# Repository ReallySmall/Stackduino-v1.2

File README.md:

Stackduino v1.2
==========
Please visit the project site for details: https://www.stackduino.net/boards/v1_2

Copyright 2017 Richard Iles

Permission is hereby granted, free of charge, to any person obtaining a copy of this software and associated documentation files (the "Software"), to deal in the Software without restriction, including without limitation the rights to use, copy, modify, merge, publish, distribute, sublicense, and/or sell copies of the Software, and to permit persons to whom the Software is furnished to do so, subject to the following conditions:

The above copyright notice and this permission notice shall be included in all copies or substantial portions of the Software.

THE SOFTWARE IS PROVIDED "AS IS", WITHOUT WARRANTY OF ANY KIND, EXPRESS OR IMPLIED, INCLUDING BUT NOT LIMITED TO THE WARRANTIES OF MERCHANTABILITY, FITNESS FOR A PARTICULAR PURPOSE AND NONINFRINGEMENT. IN NO EVENT SHALL THE AUTHORS OR COPYRIGHT HOLDERS BE LIABLE FOR ANY CLAIM, DAMAGES OR OTHER LIABILITY, WHETHER IN AN ACTION OF CONTRACT, TORT OR OTHERWISE, ARISING FROM, OUT OF OR IN CONNECTION WITH THE SOFTWARE OR THE USE OR OTHER DEALINGS IN THE SOFTWARE.

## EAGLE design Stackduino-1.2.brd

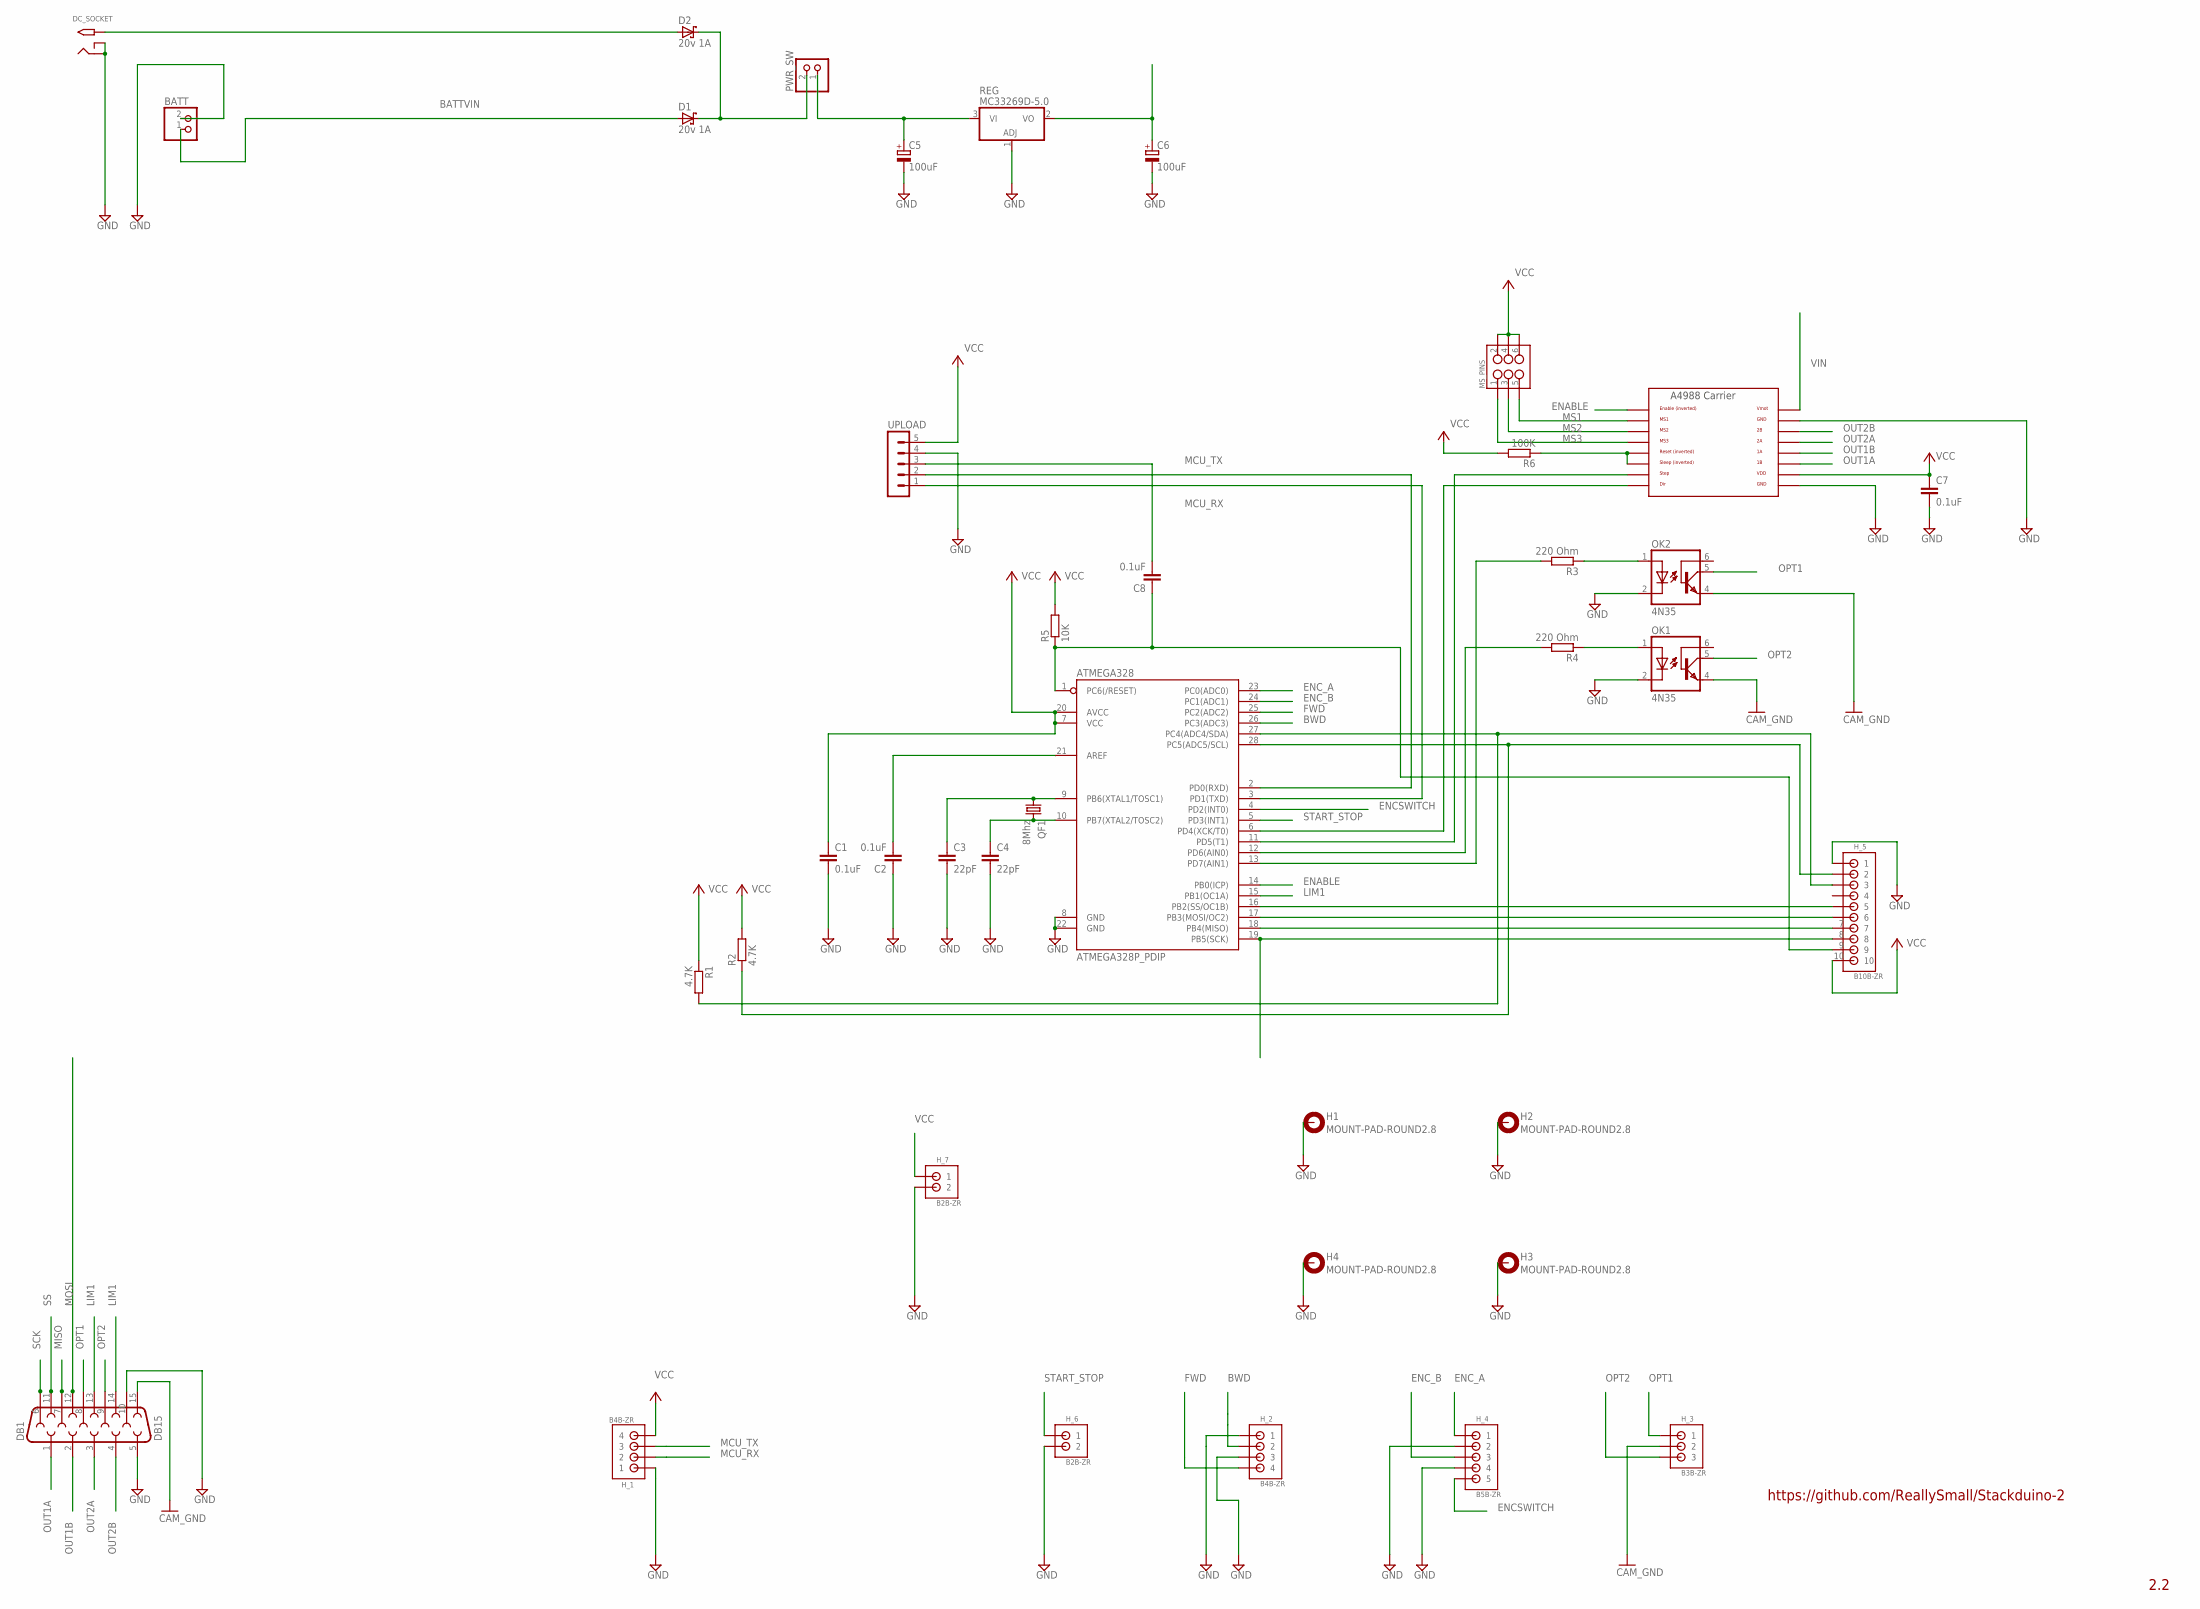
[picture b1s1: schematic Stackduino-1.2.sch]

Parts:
A4988_CARRIER: A4988BREAKOUT
ATMEGA328: ATMEGA328P_PDIP; DIL28-3
BATT: JST_2PIN-THM; JST-PH-2-THM
C1, C2, C7, C8: 0.1uF; C025-030X050
C3, C4: 22pF; C025-030X050
C5, C6: 100uF; E2,5-7
D1, D2: 20v 1A; DO41-10
DB1: DB15
DC_SOCKET: 2.1MMJACKTHM; PJ-102A
H1, H2, H3, H4: MOUNT-PAD-ROUND2.8; 2,8-PAD
H_1, H_2: B4B-ZR
H_3: B3B-ZR
H_4: B5B-ZR
H_5: B10B-ZR
H_6, H_7: B2B-ZR
MS_PINS: M03X22X3_SILK_MALE_PTH; 2X3
OK1, OK2: 4N35; DIL06
PWR_SW: JST_2PIN-THM; JST-PH-2-THM
QF1: 8Mhz; HC49U-V
R1, R2: 4.7K; 0207/7
R3, R4: 220 Ohm; 0207/7
R5: 10K; 0207/7
R6: 100K; 0207/7
REG: MC33269D-5.0; DPACK
UPLOAD: MA05-1

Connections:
A4988_RESET: A4988_CARRIER.RST, A4988_CARRIER.SLP (SLEEP), R6.1
ACVIN: D2.A, DC_SOCKET.TIP
BATTVIN: BATT.1 (2), D1.A
BWD: ATMEGA328.26 (PC3(ADC3)), H_2.2
CAM_GND: DB1.15, H_3.2, OK1.4 (EMI), OK2.4 (EMI)
DIR: A4988_CARRIER.DIR, ATMEGA328.6 (PD4(XCK/T0))
ENABLE: A4988_CARRIER.EN, ATMEGA328.14 (PB0(ICP))
ENCSWITCH: ATMEGA328.4 (PD2(INT0)), H_4.5
ENC_A: ATMEGA328.23 (PC0(ADC0)), H_4.1
ENC_B: ATMEGA328.24 (PC1(ADC1)), H_4.3
FWD: ATMEGA328.25 (PC2(ADC2)), H_2.4
GND: A4988_CARRIER.GND, A4988_CARRIER.GND@0 (GND), ATMEGA328.8 (GND), ATMEGA328.22 (GND), BATT.2 (1), C1.2, C2.1, C3.2, C4.2, C5.-, C6.-, C7.2, DB1.5, DB1.10, DC_SOCKET.RING, DC_SOCKET.RING_SW, H1.B2,8, H2.B2,8, H3.B2,8, H4.B2,8, H_1.1, H_2.1, H_2.3, H_4.2, H_4.4, H_5.1, H_6.2, H_7.2, OK1.2 (C), OK2.2 (C), REG.1 (ADJ), UPLOAD.4
I2C_SCL: ATMEGA328.28 (PC5(ADC5/SCL)), H_5.2, R2.1
I2C_SDA: ATMEGA328.27 (PC4(ADC4/SDA)), H_5.3, R1.2
LIM1: ATMEGA328.15 (PB1(OC1A)), DB1.13, DB1.14
MCU_RX: ATMEGA328.2 (PD0(RXD)), H_1.2, UPLOAD.2
MCU_TX: ATMEGA328.3 (PD1(TXD)), H_1.3, UPLOAD.1
MISO: ATMEGA328.18 (PB4(MISO)), DB1.7, H_5.7
MOSI: ATMEGA328.17 (PB3(MOSI/OC2)), DB1.12, H_5.6
MS1: A4988_CARRIER.MS1, MS_PINS.5
MS2: A4988_CARRIER.MS2, MS_PINS.3
MS3: A4988_CARRIER.MS3, MS_PINS.1
unnamed: D1.C, D2.C, PWR_SW.2 (1)
unnamed: ATMEGA328.1 (PC6(/RESET)), C8.1, H_5.9, R5.1
unnamed: C8.2, UPLOAD.3
unnamed: ATMEGA328.21 (AREF), C2.2
OPT1: DB1.8, H_3.1, OK2.5 (COL)
OPT1_IN: OK2.1 (A), R3.1
OPT1_MCU: ATMEGA328.13 (PD7(AIN1)), R3.2
OPT2: DB1.9, H_3.3, OK1.5 (COL)
OPT2_IN: OK1.1 (A), R4.1
OPT2_MCU: ATMEGA328.12 (PD6(AIN0)), R4.2
OUT1A: A4988_CARRIER.1B, DB1.1
OUT1B: A4988_CARRIER.1A, DB1.2
OUT2A: A4988_CARRIER.2A, DB1.3
OUT2B: A4988_CARRIER.2B, DB1.4
SCK: ATMEGA328.19 (PB5(SCK)), DB1.6, H_5.8
SS: ATMEGA328.16 (PB2(SS/OC1B)), DB1.11, H_5.5
START_STOP: ATMEGA328.5 (PD3(INT1)), H_6.1
STEP: A4988_CARRIER.STEP, ATMEGA328.11 (PD5(T1))
VCC: A4988_CARRIER.VDD, ATMEGA328.7 (VCC), ATMEGA328.20 (AVCC), C1.1, C6.+, C7.1, H_1.4, H_5.10, H_7.1, MS_PINS.2, MS_PINS.4, MS_PINS.6, R1.1, R2.2, R5.2, R6.2, REG.2 (VO), UPLOAD.5
VIN: A4988_CARRIER.VMOT, C5.+, PWR_SW.1 (2), REG.3 (VI)
XTAL1: ATMEGA328.9 (PB6(XTAL1/TOSC1)), C3.1, QF1.1
XTAL2: ATMEGA328.10 (PB7(XTAL2/TOSC2)), C4.1, QF1.2

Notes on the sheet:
https://github.com/ReallySmall/Stackduino-2
2.2

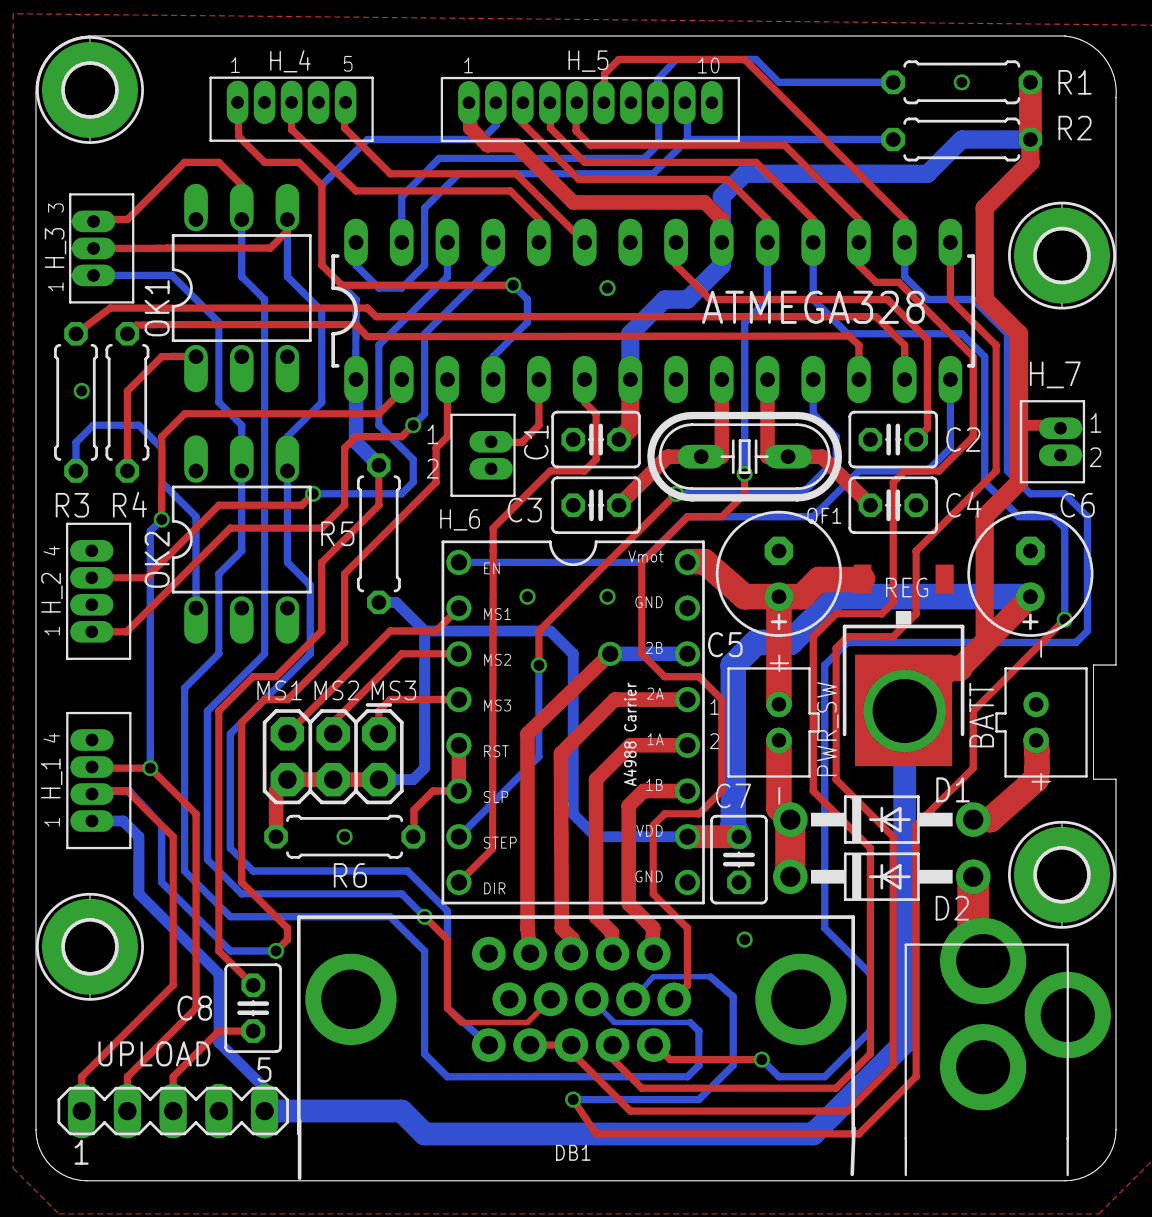
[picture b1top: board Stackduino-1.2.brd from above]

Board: 2 copper layers, 60.0 x 63.6 mm, 39 parts (0 on the bottom side), 44 nets.

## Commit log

2015-11-15 Started port of v2.2 to v1.2
2016-11-20 Added Readme
2017-01-08 Folder tidyup
2017-05-20 code now at functional level
2017-05-20 fixed return to start function
2018-09-16 Initial changes
    Added saving settings to EEPROM.
    Added/fixed limit switches support.
    Fixed settings menu.
    Moved pause after rail move and before shutter is triggered.
2018-09-16 Improved slice size UI. Split pause into pre/post capture pause.

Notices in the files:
parts and their libraries:
SparkFun-Connectors: Licensing: CC v3.0 Share-Alike You are welcome to use this library for commercial purposes.
SparkFun-DigitalIC: Licensing: Creative Commons ShareAlike 4.0 International - https://creativecommons.org/licenses/by-sa/4.0
